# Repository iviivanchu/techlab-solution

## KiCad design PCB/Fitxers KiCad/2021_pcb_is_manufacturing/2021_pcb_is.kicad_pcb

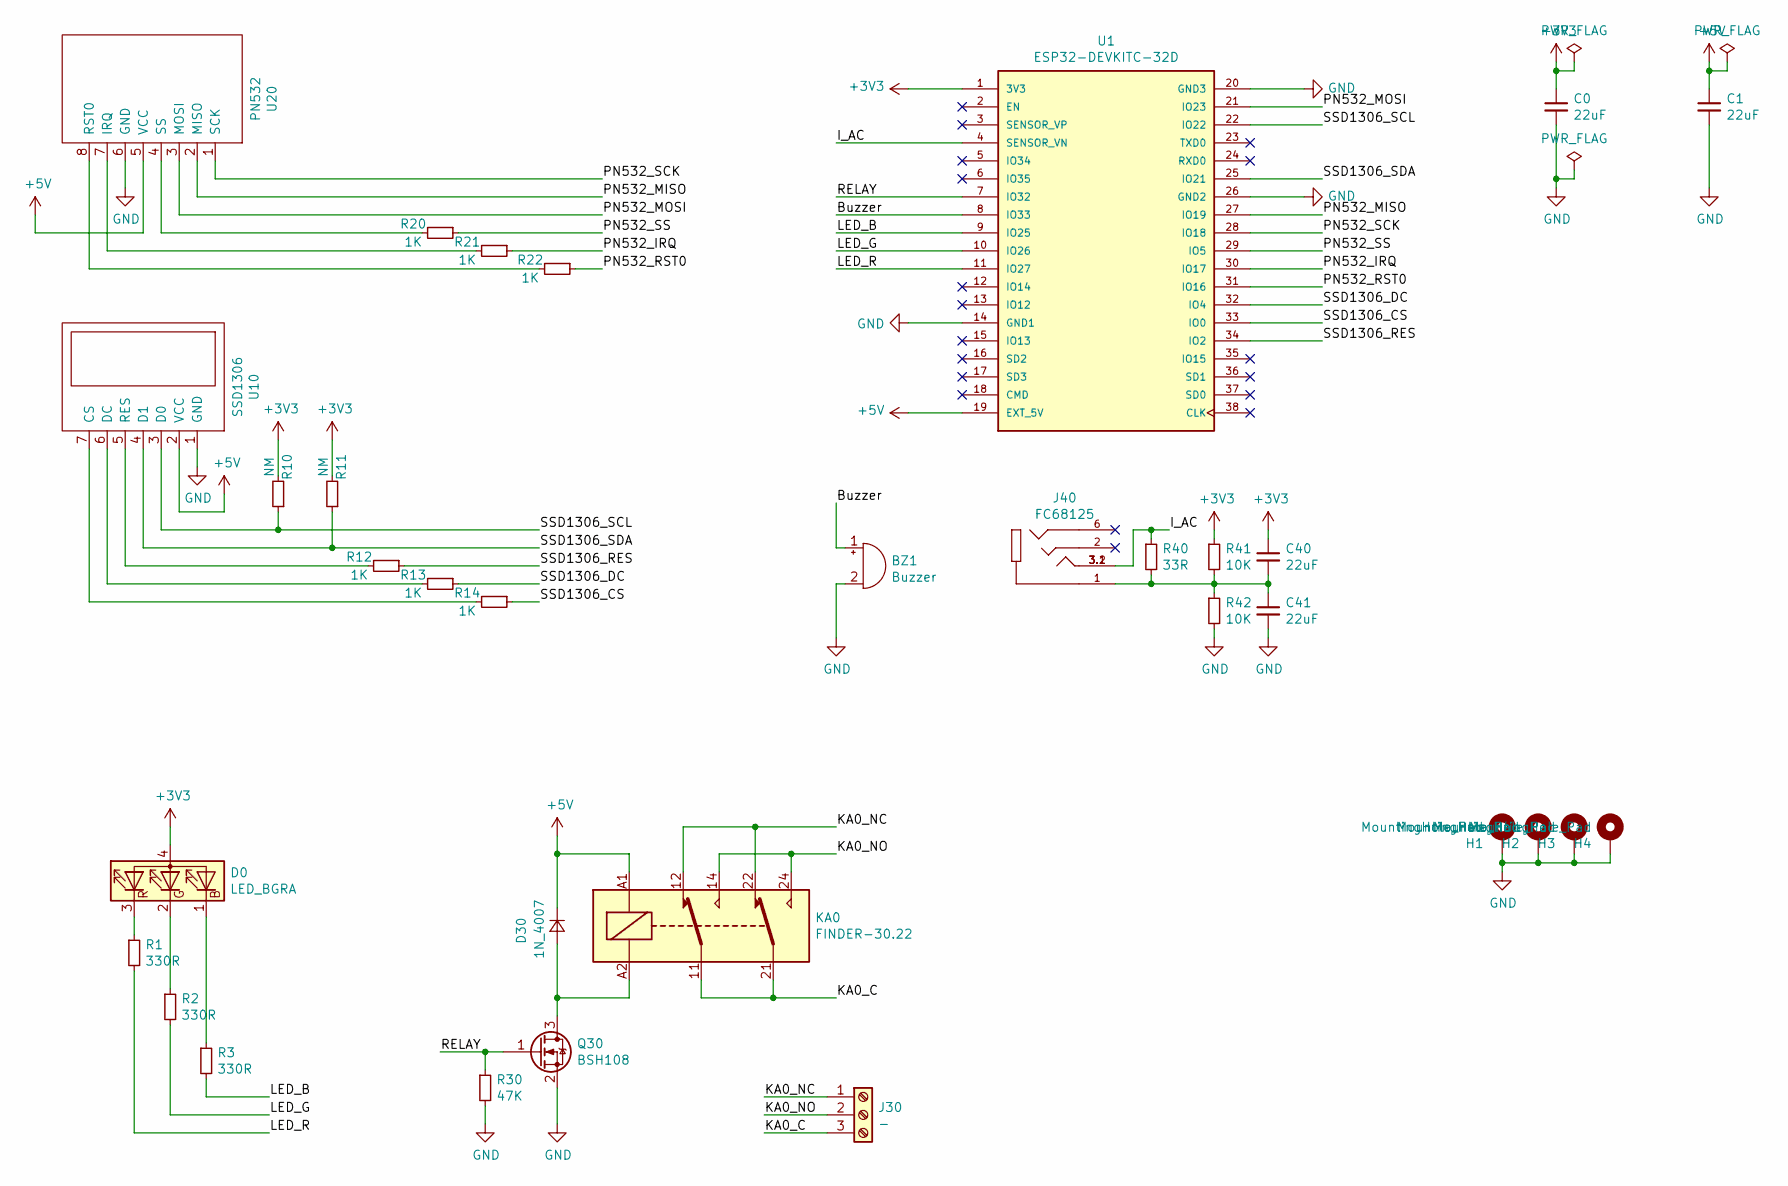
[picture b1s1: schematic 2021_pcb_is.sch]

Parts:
BZ1: Buzzer; Buzzer_15x7.5RM7.6
C0, C1, C40, C41: 22uF; C_0805_2012Metric_Pad1.15x1.40mm_HandSolder
D0: LED_BGRA; LED_Avago_PLCC4_3.2x2.8mm_CW
D30: 1N_4007; D_DO-41_SOD81_P10.16mm_Horizontal
H1, H2, H3, H4: MountingHole_Pad; MountingHole_3.2mm_M3_ISO14580_Pad
J30: -; TerminalBlock_RND_205-00013_1x03_P5.00mm_Horizontal
J40: FC68125; CLIFF_FC68125
KA0: FINDER-30.22; Relay_DPDT_Finder_30.22
Q30: BSH108; SOT-23
R1, R2, R3: 330R; R_0805_2012Metric_Pad1.15x1.40mm_HandSolder
R10, R11: NM; R_0805_2012Metric_Pad1.15x1.40mm_HandSolder
R12, R13, R14, R20, R21, R22: 1K; R_0805_2012Metric_Pad1.15x1.40mm_HandSolder
R30: 47K; R_0805_2012Metric_Pad1.15x1.40mm_HandSolder
R40: 33R; R_0805_2012Metric_Pad1.15x1.40mm_HandSolder
R41, R42: 10K; R_0805_2012Metric_Pad1.15x1.40mm_HandSolder
U1: ESP32-DEVKITC-32D; MODULE_ESP32-DEVKITC-32D; PARTREV 4
U10: SSD1306; SSD1306_2H
U20: PN532; PN532_N3D_3

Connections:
+3V3: C0.1, C40.1, D0.4 (A), R10.2, R11.2, R41.1, U1.1 (3V3)
+5V: C1.1, D30.1 (K), KA0.A1, U1.19 (EXT_5V), U10.2 (VCC), U20.5 (VCC)
/Buzzer: BZ1.1 (-), U1.8 (IO33)
/I_AC: J40.3.1 (3T), J40.3.2 (3T), R40.1, U1.4 (SENSOR_VN)
/KA0_C: J30.3, KA0.11, KA0.21
/KA0_NC: J30.1, KA0.12, KA0.22
/KA0_NO: J30.2, KA0.14, KA0.24
/LED_B: R3.2, U1.9 (IO25)
/LED_G: R2.2, U1.10 (IO26)
/LED_R: R1.2, U1.11 (IO27)
/PN532_IRQ: R21.1, U1.30 (IO17)
/PN532_MISO: U1.27 (IO19), U20.2 (MISO)
/PN532_MOSI: U1.21 (IO23), U20.3 (MOSI)
/PN532_RST0: R22.1, U1.31 (IO16)
/PN532_SCK: U1.28 (IO18), U20.1 (SCK)
/PN532_SS: R20.1, U1.29 (IO5)
/RELAY: Q30.1 (G), R30.1, U1.7 (IO32)
/SSD1306_CS: R14.1, U1.33 (IO0)
/SSD1306_DC: R13.1, U1.32 (IO4)
/SSD1306_RES: R12.1, U1.34 (IO2)
/SSD1306_SCL: R10.1, U1.22 (IO22), U10.3 (D0)
/SSD1306_SDA: R11.1, U1.25 (IO21), U10.4 (D1)
GND: BZ1.2 (+), C0.2, C1.2, C41.2, H1.1, H2.1, H3.1, H4.1, Q30.2 (S), R30.2, R42.2, U1.14 (GND1), U1.20 (GND3), U1.26 (GND2), U10.1 (GND), U20.6 (GND)
unnamed: C40.2, C41.1, J40.1 (1S), R40.2, R41.2, R42.1
unnamed: D0.1 (BK), R3.1
unnamed: D0.2 (GK), R2.1
unnamed: D0.3 (RK), R1.1
unnamed: D30.2 (A), KA0.A2, Q30.3 (D)
unnamed: R12.2, U10.5 (RES)
unnamed: R13.2, U10.6 (DC)
unnamed: R14.2, U10.7 (CS)
unnamed: R20.2, U20.4 (SS)
unnamed: R21.2, U20.7 (IRQ)
unnamed: R22.2, U20.8 (RST0)

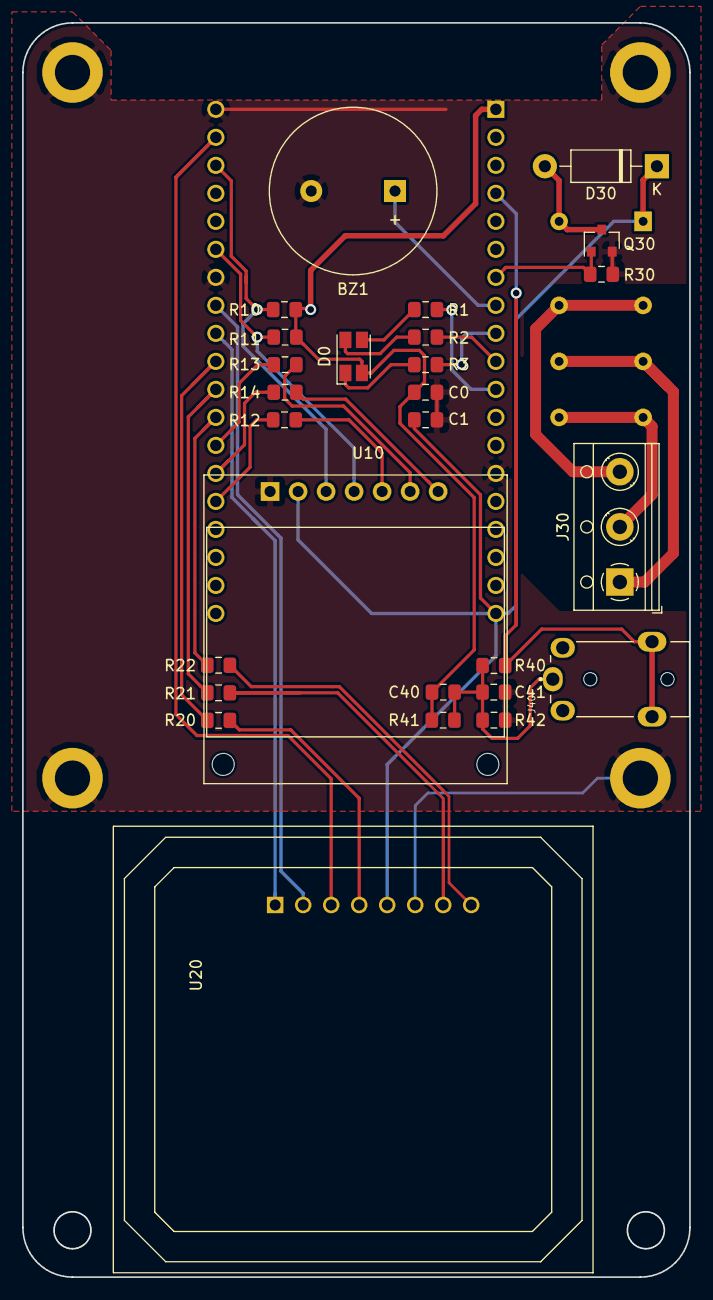
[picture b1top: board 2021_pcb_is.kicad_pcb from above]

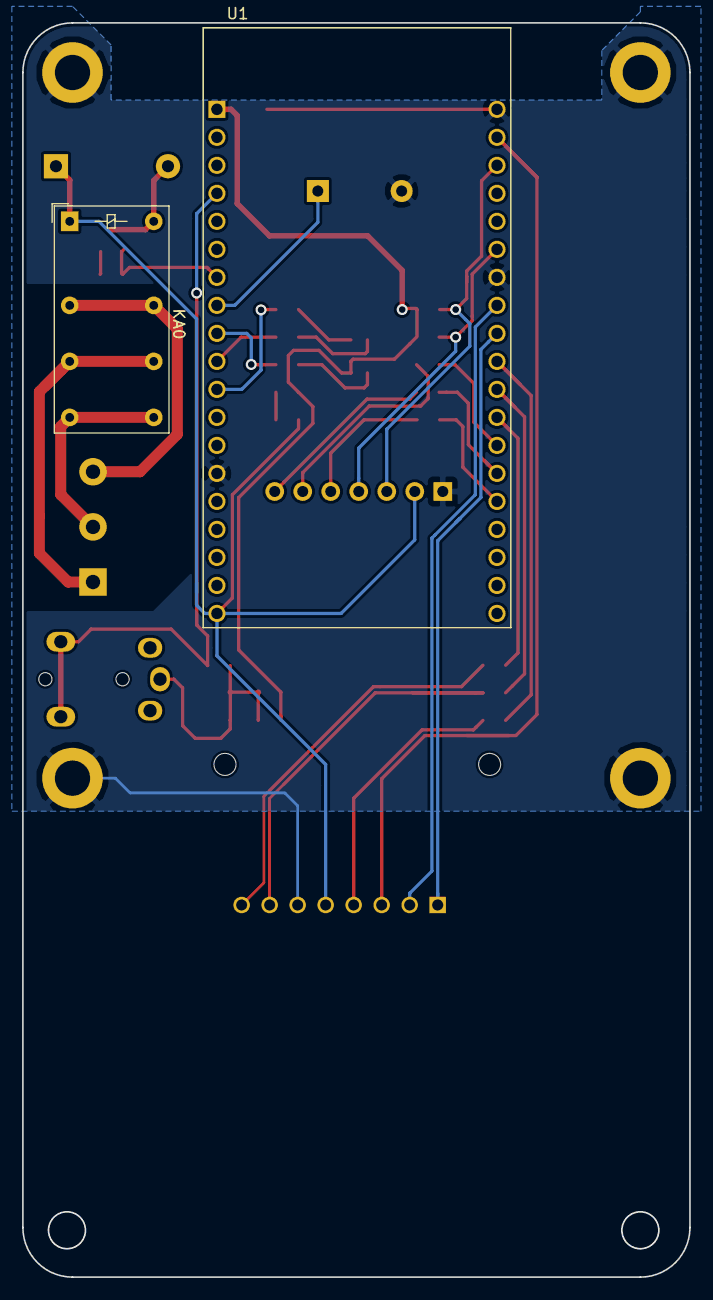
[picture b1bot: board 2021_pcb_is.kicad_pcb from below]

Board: 2 copper layers, 60.5 x 113.8 mm, 33 parts (2 on the bottom side), 34 nets.

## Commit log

2022-01-31 Add files via upload
    Proyecto subido.
2022-01-31 Create SERVER
    Carpeta del servidor creada.
2022-01-31 Add files via upload
    Servidor subido.
2022-02-23 Añadido un archivo
2022-02-23 Eliminado Hola
2022-02-23 Resubiendo todo
2022-02-23 New project updated
